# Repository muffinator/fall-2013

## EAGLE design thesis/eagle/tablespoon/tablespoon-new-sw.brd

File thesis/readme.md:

Welcome to the future of breadboarding

This is Butter

To operate the simulation files (rlc or ac.py), you need:
NGspice (nutmeg!) and you need to add it to your system path

Before looking at index.html, run an HTTP server from this directory.

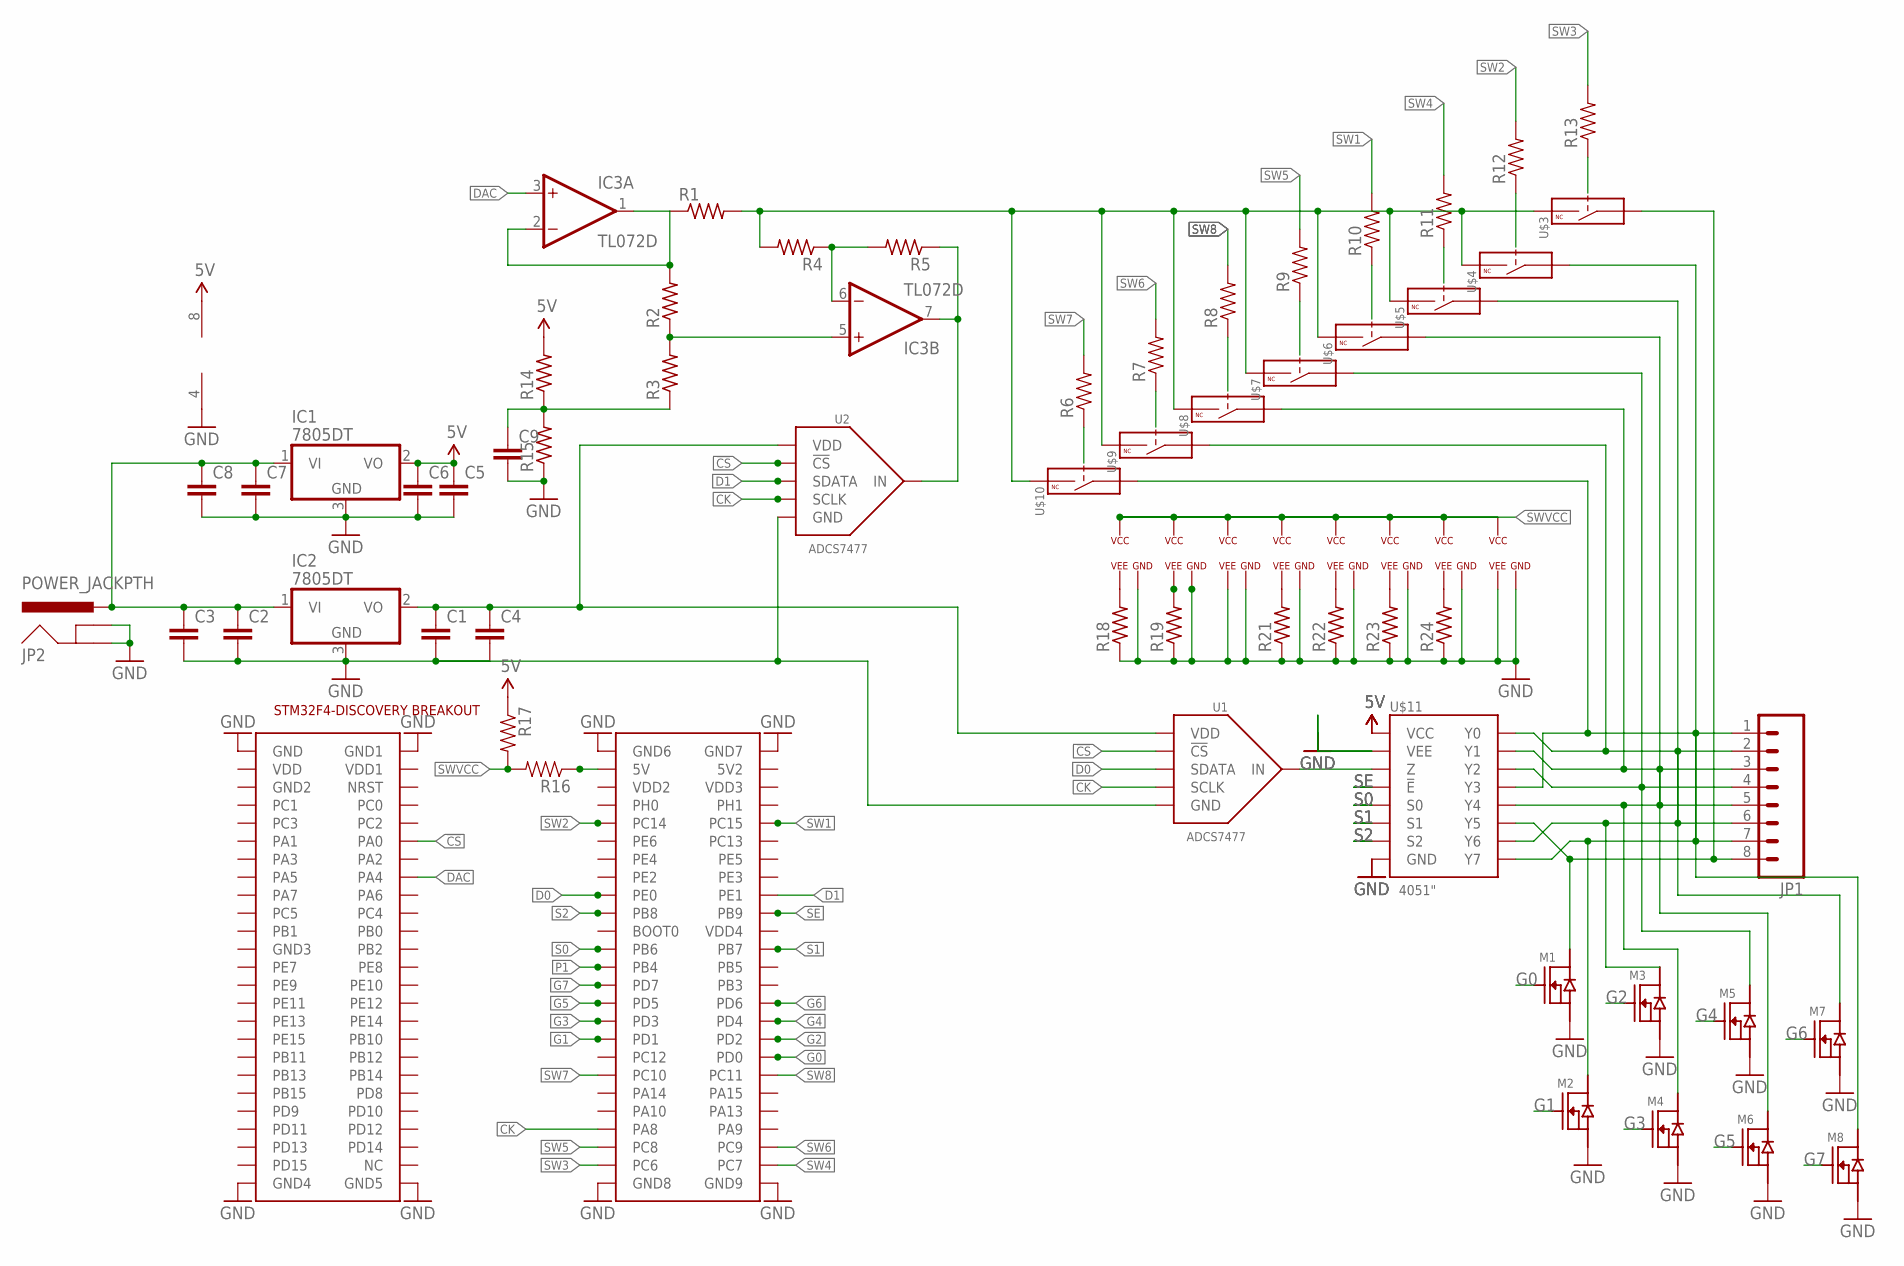
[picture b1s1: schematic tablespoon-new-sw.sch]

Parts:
C1, C2, C3, C4, C5, C6, C7, C8: C-EUC0805; C0805
C9: C-EUC0603; C0603
IC1, IC2: 7805DT; TO252
IC3: TL072D; SO08
JP1: M08LONGPADS; 1X08_LONGPADS
JP2: POWER_JACKPTH; POWER_JACK_PTH
M1, M2, M3, M4, M5, M6, M7, M8: N-FET; SOT23-3
R1, R2, R3, R4, R5, R14, R15, R18, R19, R21, R22, R23, R24: R-US_R0603; R0603
R6, R7, R8, R9, R10, R11, R12, R13, R16, R17: RESISTOR0805-RES; 0805
U1, U2: ADCS7477; SOT-23-6
U$1: STM32F4-DISCOVERY
U$3, U$4, U$5, U$6, U$7, U$8, U$9, U$10: DG467DG9422; TSSOP-6
U$11: 4051"; TSSOP-16

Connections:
4.6V: R16.1, U$1.P$53 (5V)
5V: C5.1, C6.1, IC1.2 (VO), IC3.8 (V+), R14.2, R17.1, U$11.P$16 (VCC)
!CS: U1.P$6 (!CS), U2.P$6 (!CS), U$1.P$12 (PA0)
CK: U1.P$4 (SCLK), U2.P$4 (SCLK), U$1.P$93 (PA8)
CUR: IC3.7 (OUT), R5.1, U2.P$3 (IN)
D0: U1.P$5 (SDATA), U$1.P$67 (PE0)
D1: U2.P$5 (SDATA), U$1.P$68 (PE1)
DAC: IC3.3 (+IN), U$1.P$16 (PA4)
G0: M1.1 (G), U$1.P$86 (PD0)
G1: M2.1 (G), U$1.P$83 (PD1)
G2: M3.1 (G), U$1.P$84 (PD2)
G3: M4.1 (G), U$1.P$81 (PD3)
G4: M5.1 (G), U$1.P$82 (PD4)
G5: M6.1 (G), U$1.P$79 (PD5)
G6: M7.1 (G), U$1.P$80 (PD6)
G7: M8.1 (G), U$1.P$77 (PD7)
GND: C1.2, C2.2, C3.2, C4.2, C5.2, C6.2, C7.2, C8.2, C9.2, IC1.3 (GND), IC2.3 (GND), IC3.4 (V-), JP2.GND, JP2.GNDBREAK, M1.2 (S), M2.2 (S), M3.2 (S), M4.2 (S), M5.2 (S), M6.2 (S), M7.2 (S), M8.2 (S), R15.1, R18.1, R19.1, R21.1, R22.1, R23.1, R24.1, U1.P$2 (GND), U2.P$2 (GND), U$1.P$1 (GND), U$1.P$2 (GND1), U$1.P$49 (GND4), U$1.P$50 (GND5), U$1.P$51 (GND6), U$1.P$52 (GND7), U$1.P$99 (GND8), U$1.P$100 (GND9), U$3.P$3 (VEE), U$3.P$4 (GND), U$4.P$4 (GND), U$5.P$4 (GND), U$6.P$4 (GND), U$7.P$4 (GND), U$8.P$4 (GND), U$9.P$4 (GND), U$10.P$3 (VEE), U$10.P$4 (GND), U$11.P$7 (VEE), U$11.P$8 (GND)
unnamed: JP1.2, M7.3 (D), U$9.P$2 (COM), U$11.P$13 (Y0)
unnamed: C1.1, C4.1, IC2.2 (VO), U1.P$1 (VDD), U2.P$1 (VDD)
unnamed: R6.1, U$10.P$6 (CTL)
unnamed: C2.1, C3.1, C7.1, C8.1, IC1.1 (VI), IC2.1 (VI), JP2.PWR
unnamed: JP1.3, M6.3 (D), U$8.P$2 (COM), U$11.P$14 (Y1)
unnamed: R7.1, U$9.P$6 (CTL)
unnamed: IC3.1 (OUT), IC3.2 (-IN), R1.1, R2.2
unnamed: JP1.1, M8.3 (D), U$10.P$2 (COM), U$11.P$12 (Y3)
unnamed: IC3.5 (+IN), R2.1, R3.2
unnamed: IC3.6 (-IN), R4.1, R5.2
unnamed: R8.1, U$8.P$6 (CTL)
unnamed: R1.2, R4.2, U$3.P$5 (IN), U$4.P$5 (IN), U$5.P$5 (IN), U$6.P$5 (IN), U$7.P$5 (IN), U$8.P$5 (IN), U$9.P$5 (IN), U$10.P$5 (IN)
unnamed: R9.1, U$7.P$6 (CTL)
unnamed: R12.1, U$4.P$6 (CTL)
unnamed: R13.1, U$3.P$6 (CTL)
unnamed: R11.1, U$5.P$6 (CTL)
unnamed: R10.1, U$6.P$6 (CTL)
unnamed: JP1.8, M1.3 (D), U$3.P$2 (COM), U$11.P$5 (Y5)
unnamed: C9.1, R3.1, R14.1, R15.2
unnamed: U1.P$3 (IN), U$11.P$3 (Z)
unnamed: JP1.7, M2.3 (D), U$4.P$2 (COM), U$11.P$4 (Y7)
unnamed: JP1.6, M3.3 (D), U$5.P$2 (COM), U$11.P$2 (Y6)
unnamed: JP1.5, M4.3 (D), U$6.P$2 (COM), U$11.P$1 (Y4)
unnamed: JP1.4, M5.3 (D), U$7.P$2 (COM), U$11.P$15 (Y2)
unnamed: R18.2, U$9.P$3 (VEE)
unnamed: R19.2, U$8.P$3 (VEE)
unnamed: R21.2, U$4.P$3 (VEE)
unnamed: R22.2, U$5.P$3 (VEE)
unnamed: R23.2, U$6.P$3 (VEE)
unnamed: R24.2, U$7.P$3 (VEE)
P1: U$1.P$75 (PB4)
S0: U$1.P$73 (PB6), U$11.P$11 (S0)
S1: U$1.P$74 (PB7), U$11.P$10 (S1)
S2: U$1.P$69 (PB8), U$11.P$9 (S2)
SE: U$1.P$70 (PB9), U$11.P$6 (!E)
SW1: R10.2, U$1.P$60 (PC15)
SW2: R12.2, U$1.P$59 (PC14)
SW3: R13.2, U$1.P$97 (PC6)
SW4: R11.2, U$1.P$98 (PC7)
SW5: R9.2, U$1.P$95 (PC8)
SW6: R7.2, U$1.P$96 (PC9)
SW7: R6.2, U$1.P$87 (PC10)
SW8: R8.2, U$1.P$88 (PC11)
SWVCC: R16.2, R17.2, U$3.P$1 (VCC), U$4.P$1 (VCC), U$5.P$1 (VCC), U$6.P$1 (VCC), U$7.P$1 (VCC), U$8.P$1 (VCC), U$9.P$1 (VCC), U$10.P$1 (VCC)

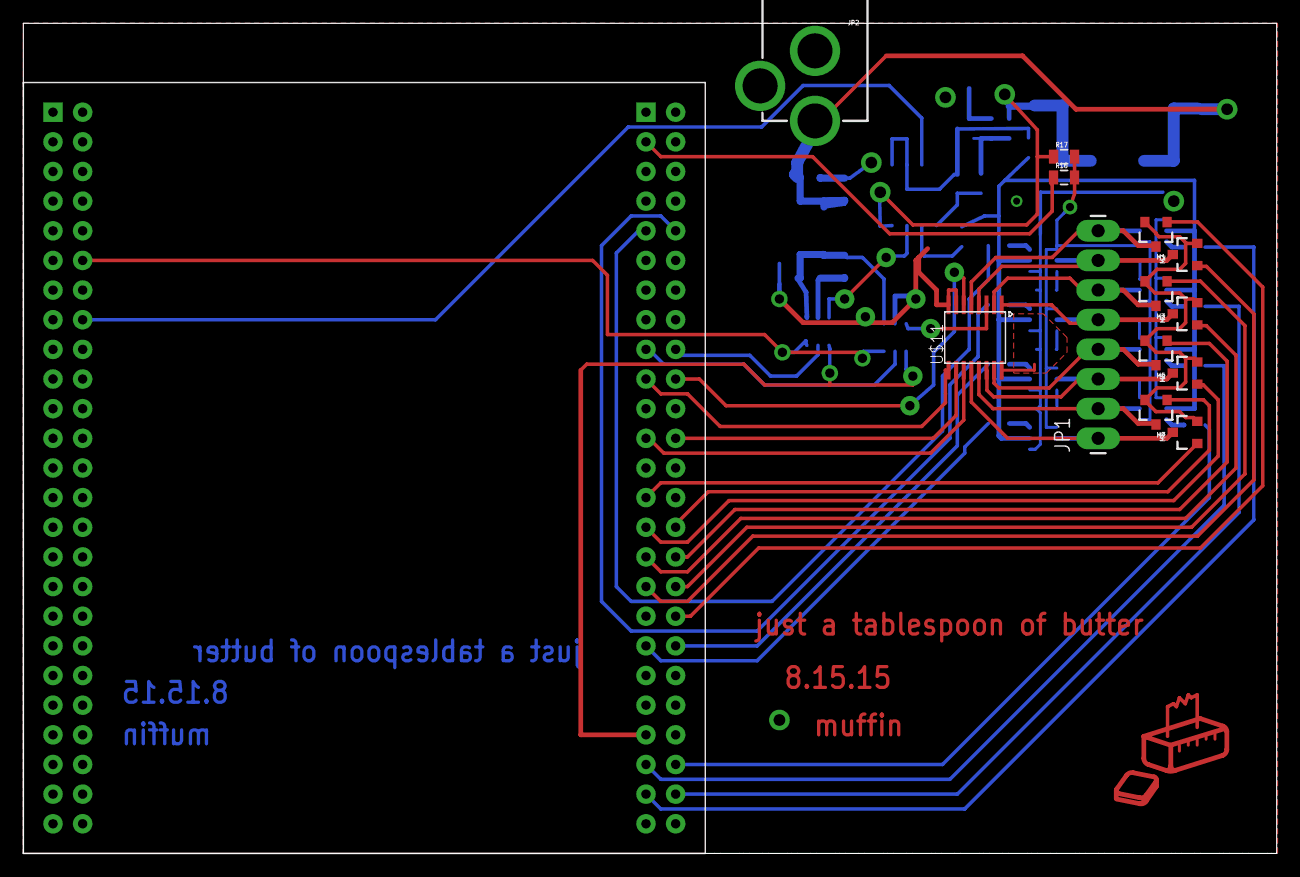
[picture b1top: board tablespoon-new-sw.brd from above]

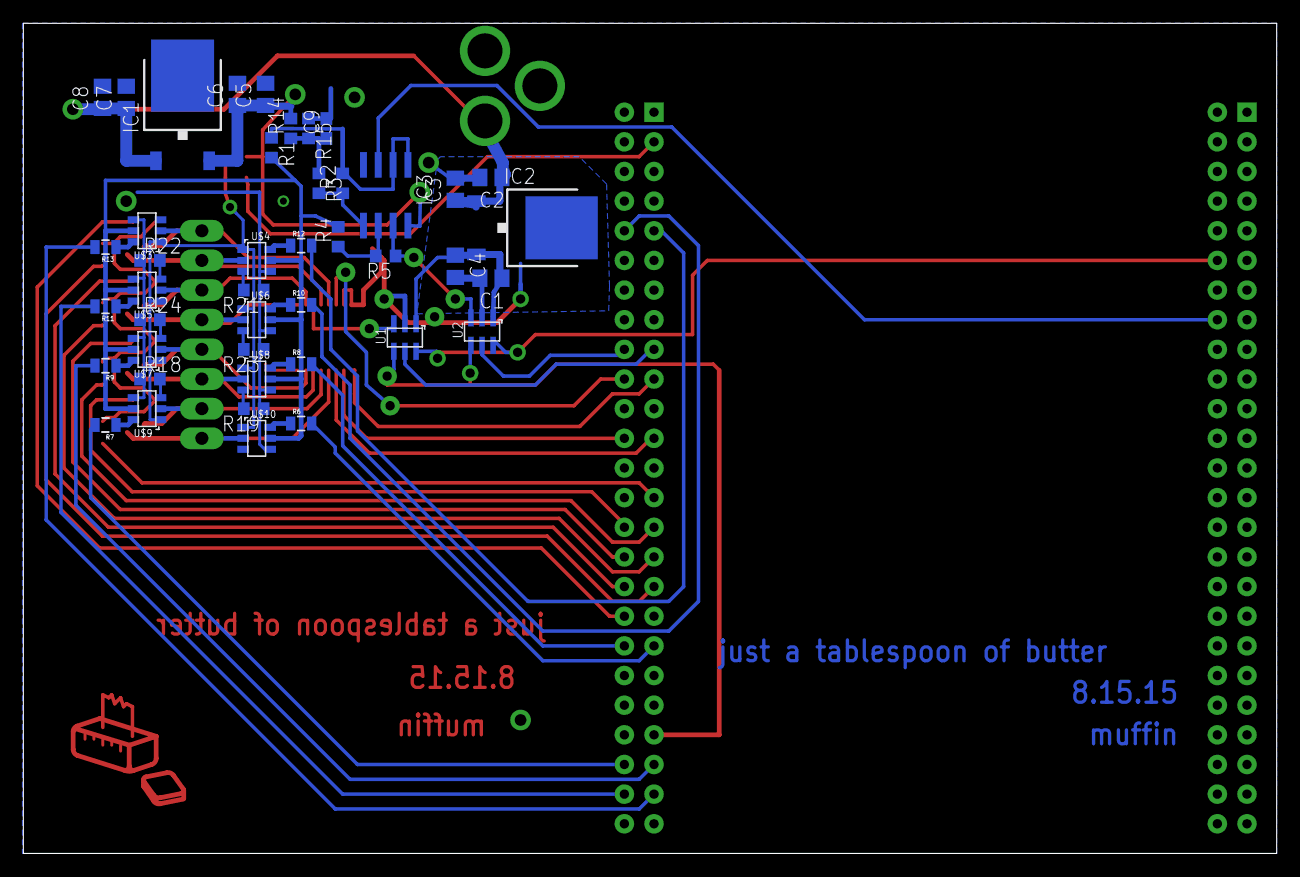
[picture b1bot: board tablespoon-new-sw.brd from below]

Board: 2 copper layers, 107.4 x 71.1 mm, 57 parts (43 on the bottom side), 60 nets.

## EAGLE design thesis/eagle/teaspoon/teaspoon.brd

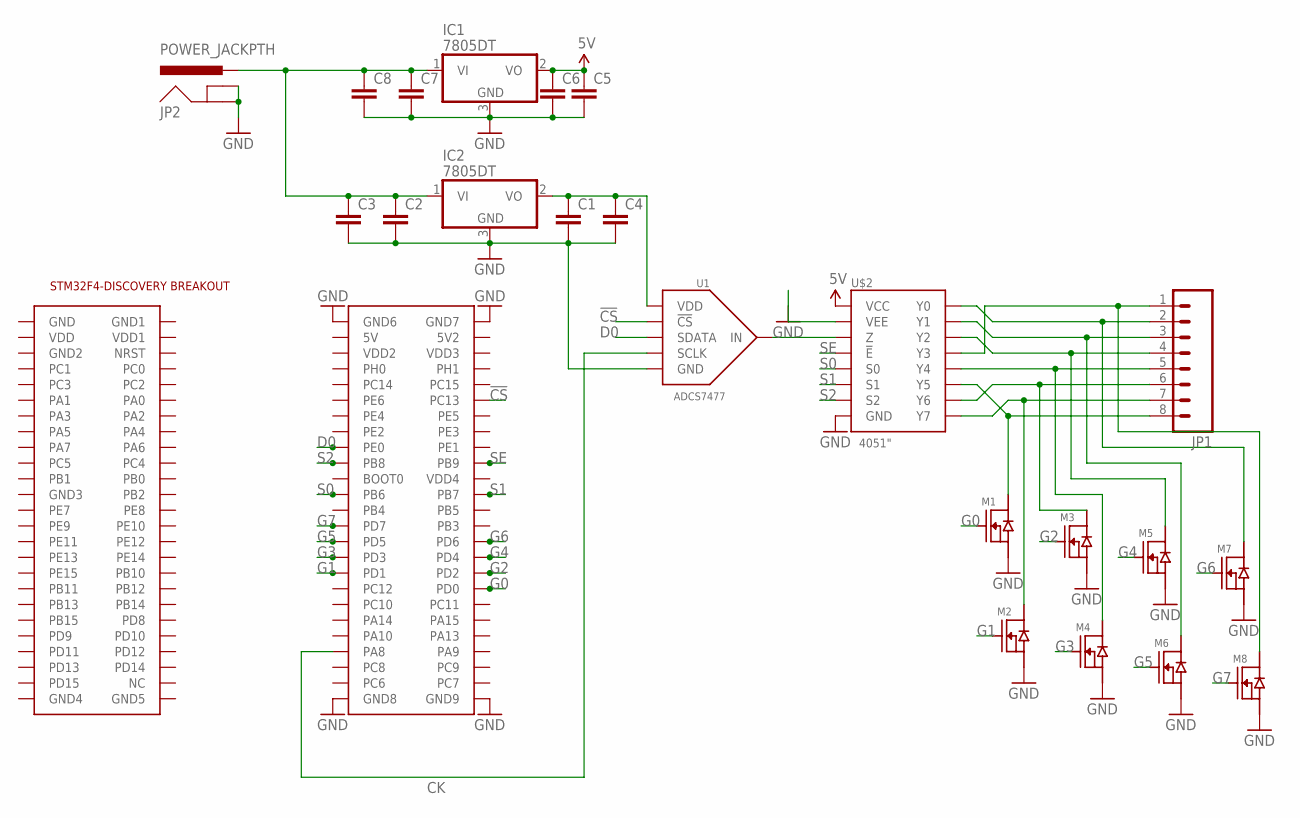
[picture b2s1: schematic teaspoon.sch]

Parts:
C1, C2, C3, C4, C5, C6, C7, C8: C-EUC0805; C0805
IC1, IC2: 7805DT; TO252
JP1: M08LONGPADS; 1X08_LONGPADS
JP2: POWER_JACKPTH; POWER_JACK_PTH
M1, M2, M3, M4, M5, M6, M7, M8: N-FET; SOT23-3
U1: ADCS7477; SOT-23-6
U$1: STM32F4-DISCOVERY
U$2: 4051"; TSSOP-16

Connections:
5V: C5.1, C6.1, IC1.2 (VO), U$2.P$16 (VCC)
!CS: U1.P$6 (!CS), U$1.P$62 (PC13)
CK: U1.P$4 (SCLK), U$1.P$93 (PA8)
D0: U1.P$5 (SDATA), U$1.P$67 (PE0)
G0: M1.1 (G), U$1.P$86 (PD0)
G1: M2.1 (G), U$1.P$83 (PD1)
G2: M3.1 (G), U$1.P$84 (PD2)
G3: M4.1 (G), U$1.P$81 (PD3)
G4: M5.1 (G), U$1.P$82 (PD4)
G5: M6.1 (G), U$1.P$79 (PD5)
G6: M7.1 (G), U$1.P$80 (PD6)
G7: M8.1 (G), U$1.P$77 (PD7)
GND: C1.2, C2.2, C3.2, C4.2, C5.2, C6.2, C7.2, C8.2, IC1.3 (GND), IC2.3 (GND), JP2.GND, JP2.GNDBREAK, M1.2 (S), M2.2 (S), M3.2 (S), M4.2 (S), M5.2 (S), M6.2 (S), M7.2 (S), M8.2 (S), U1.P$2 (GND), U$1.P$51 (GND6), U$1.P$52 (GND7), U$1.P$99 (GND8), U$1.P$100 (GND9), U$2.P$7 (VEE), U$2.P$8 (GND)
unnamed: U1.P$3 (IN), U$2.P$3 (Z)
unnamed: C1.1, C4.1, IC2.2 (VO), U1.P$1 (VDD)
unnamed: C2.1, C3.1, C7.1, C8.1, IC1.1 (VI), IC2.1 (VI), JP2.PWR
unnamed: JP1.1, M8.3 (D), U$2.P$12 (Y3)
unnamed: JP1.2, M7.3 (D), U$2.P$13 (Y0)
unnamed: JP1.3, M6.3 (D), U$2.P$14 (Y1)
unnamed: JP1.4, M5.3 (D), U$2.P$15 (Y2)
unnamed: JP1.5, M4.3 (D), U$2.P$1 (Y4)
unnamed: JP1.6, M3.3 (D), U$2.P$2 (Y6)
unnamed: JP1.7, M2.3 (D), U$2.P$4 (Y7)
unnamed: JP1.8, M1.3 (D), U$2.P$5 (Y5)
S0: U$1.P$73 (PB6), U$2.P$11 (S0)
S1: U$1.P$74 (PB7), U$2.P$10 (S1)
S2: U$1.P$69 (PB8), U$2.P$9 (S2)
SE: U$1.P$70 (PB9), U$2.P$6 (!E)

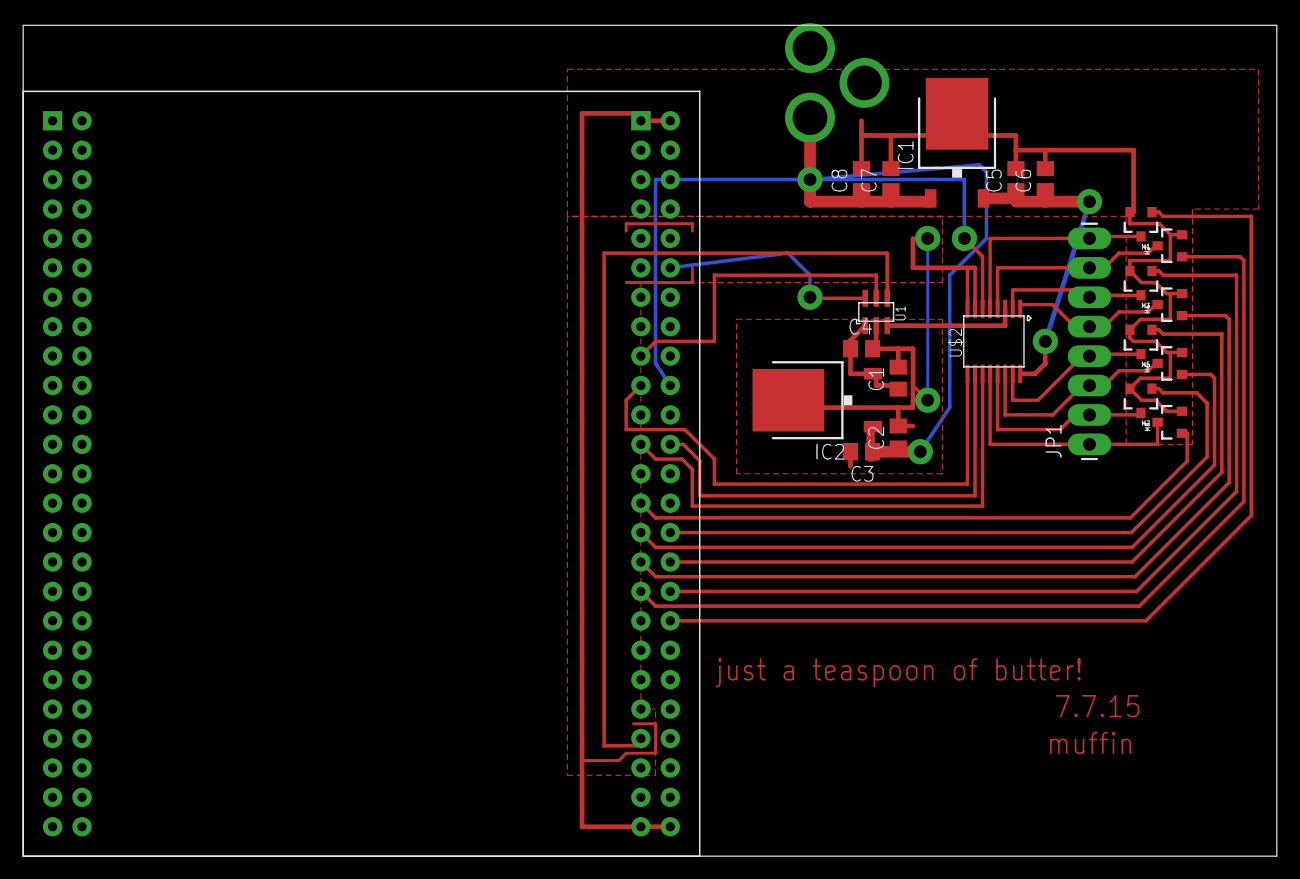
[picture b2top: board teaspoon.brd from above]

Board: 2 copper layers, 108.3 x 71.7 mm, 23 parts (1 on the bottom side), 28 nets.

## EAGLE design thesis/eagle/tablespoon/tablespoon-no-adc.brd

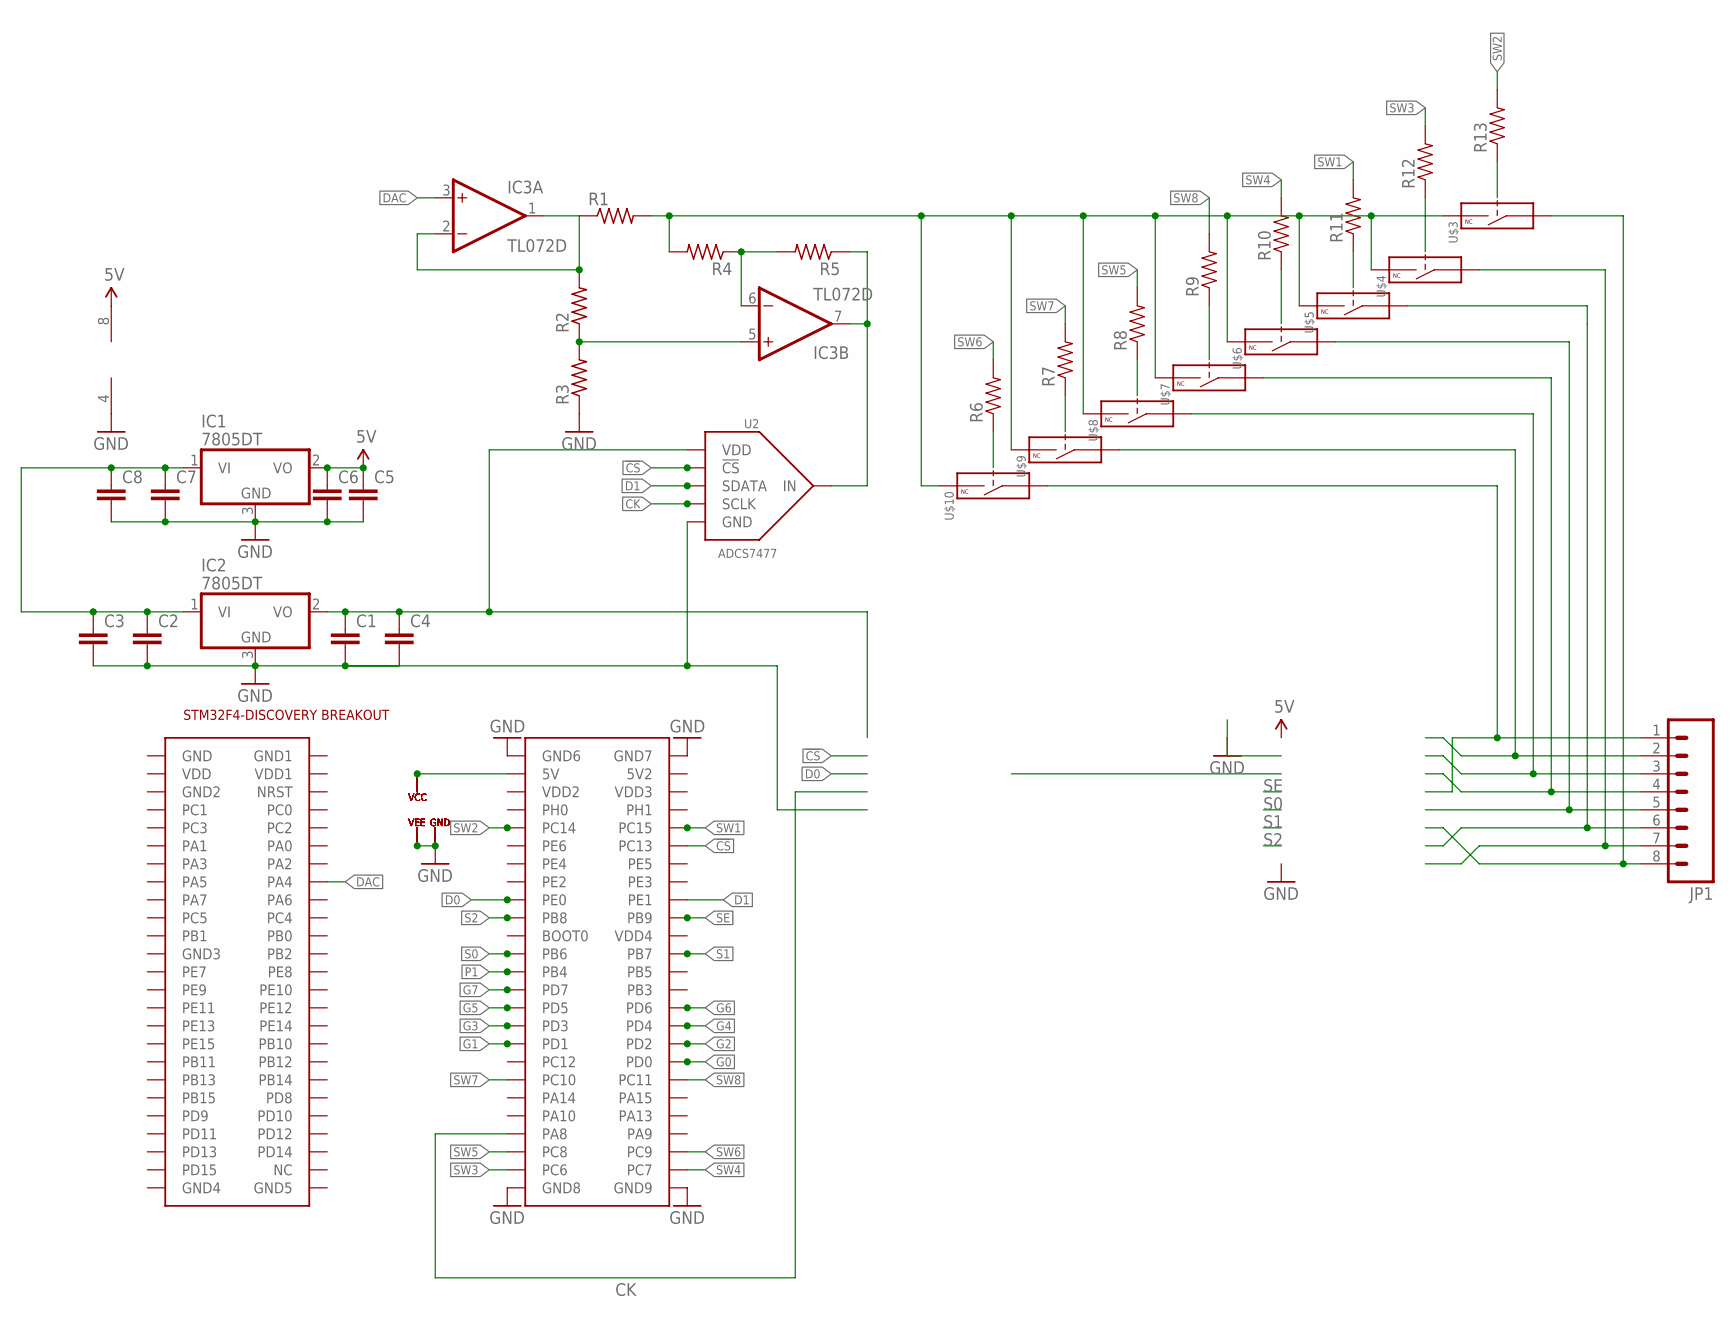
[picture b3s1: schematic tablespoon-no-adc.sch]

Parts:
C1, C2, C3, C4, C5, C6, C7, C8: C-EUC0805; C0805
IC1, IC2: 7805DT; TO252
IC3: TL072D; SO08
JP1: M08LONGPADS; 1X08_LONGPADS
R1, R2, R3, R4, R5: R-US_R0603; R0603
R6, R7, R8, R9, R10, R11, R12, R13: RESISTOR0805-RES; 0805
U2: ADCS7477; SOT-23-6
U$1: STM32F4-DISCOVERY
U$3, U$4, U$5, U$6, U$7, U$8, U$9, U$10: DG467; TSSOP-6

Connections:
4.6V: U$1.P$53 (5V), U$3.P$5 (VCC), U$4.P$5 (VCC), U$5.P$5 (VCC), U$6.P$5 (VCC), U$7.P$5 (VCC), U$8.P$5 (VCC), U$9.P$5 (VCC), U$10.P$5 (VCC)
5V: C5.1, C6.1, IC1.2 (VO), IC3.8 (V+)
!CS: U2.P$6 (!CS), U$1.P$62 (PC13)
CK: U2.P$4 (SCLK), U$1.P$93 (PA8)
CUR: IC3.7 (OUT), R5.1, U2.P$3 (IN)
D0: U$1.P$67 (PE0)
D1: U2.P$5 (SDATA), U$1.P$68 (PE1)
DAC: IC3.3 (+IN), U$1.P$16 (PA4)
G0: U$1.P$86 (PD0)
G1: U$1.P$83 (PD1)
G2: U$1.P$84 (PD2)
G3: U$1.P$81 (PD3)
G4: U$1.P$82 (PD4)
G5: U$1.P$79 (PD5)
G6: U$1.P$80 (PD6)
G7: U$1.P$77 (PD7)
GND: C1.2, C2.2, C3.2, C4.2, C5.2, C6.2, C7.2, C8.2, IC1.3 (GND), IC2.3 (GND), IC3.4 (V-), R3.1, U2.P$2 (GND), U$1.P$51 (GND6), U$1.P$52 (GND7), U$1.P$99 (GND8), U$1.P$100 (GND9), U$3.P$2 (VEE), U$3.P$4 (GND), U$4.P$2 (VEE), U$4.P$4 (GND), U$5.P$2 (VEE), U$5.P$4 (GND), U$6.P$2 (VEE), U$6.P$4 (GND), U$7.P$2 (VEE), U$7.P$4 (GND), U$8.P$2 (VEE), U$8.P$4 (GND), U$9.P$2 (VEE), U$9.P$4 (GND), U$10.P$2 (VEE), U$10.P$4 (GND)
unnamed: C1.1, C4.1, IC2.2 (VO), U2.P$1 (VDD)
unnamed: R6.1, U$10.P$3 (CTL)
unnamed: C2.1, C3.1, C7.1, C8.1, IC1.1 (VI), IC2.1 (VI)
unnamed: JP1.4, U$7.P$6 (COM)
unnamed: R7.1, U$9.P$3 (CTL)
unnamed: IC3.1 (OUT), IC3.2 (-IN), R1.1, R2.2
unnamed: JP1.5, U$6.P$6 (COM)
unnamed: JP1.3, U$8.P$6 (COM)
unnamed: JP1.1, U$10.P$6 (COM)
unnamed: JP1.2, U$9.P$6 (COM)
unnamed: IC3.5 (+IN), R2.1, R3.2
unnamed: IC3.6 (-IN), R4.1, R5.2
unnamed: R8.1, U$8.P$3 (CTL)
unnamed: R1.2, R4.2, U$3.P$1 (IN), U$4.P$1 (IN), U$5.P$1 (IN), U$6.P$1 (IN), U$7.P$1 (IN), U$8.P$1 (IN), U$9.P$1 (IN), U$10.P$1 (IN)
unnamed: R9.1, U$7.P$3 (CTL)
unnamed: R12.1, U$4.P$3 (CTL)
unnamed: R13.1, U$3.P$3 (CTL)
unnamed: R11.1, U$5.P$3 (CTL)
unnamed: R10.1, U$6.P$3 (CTL)
unnamed: JP1.6, U$5.P$6 (COM)
unnamed: JP1.7, U$4.P$6 (COM)
unnamed: JP1.8, U$3.P$6 (COM)
P1: U$1.P$75 (PB4)
S0: U$1.P$73 (PB6)
S1: U$1.P$74 (PB7)
S2: U$1.P$69 (PB8)
SE: U$1.P$70 (PB9)
SW1: R11.2, U$1.P$60 (PC15)
SW2: R13.2, U$1.P$59 (PC14)
SW3: R12.2, U$1.P$97 (PC6)
SW4: R10.2, U$1.P$98 (PC7)
SW5: R8.2, U$1.P$95 (PC8)
SW6: R6.2, U$1.P$96 (PC9)
SW7: R7.2, U$1.P$87 (PC10)
SW8: R9.2, U$1.P$88 (PC11)

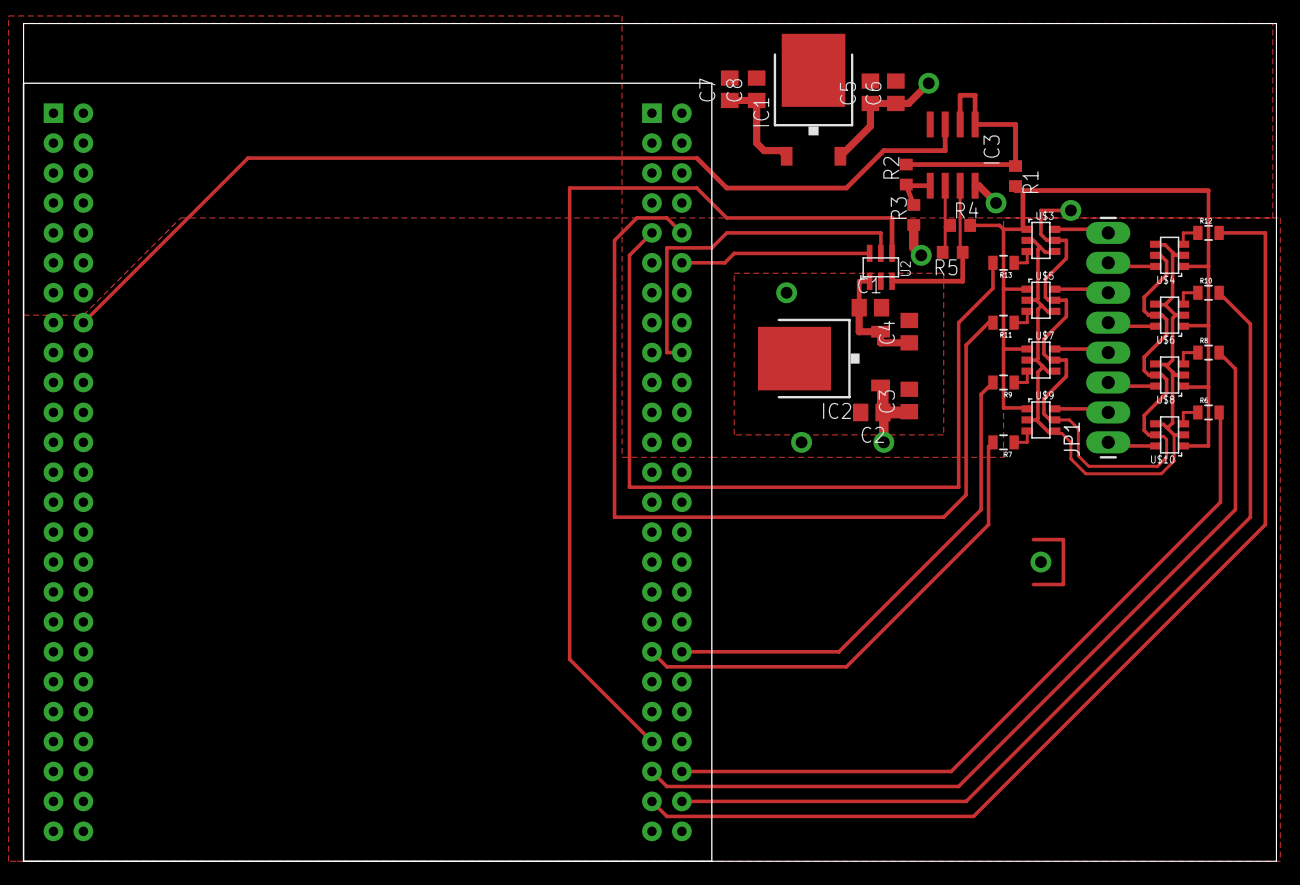
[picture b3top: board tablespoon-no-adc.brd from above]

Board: 2 copper layers, 106.3 x 71.1 mm, 35 parts (0 on the bottom side), 38 nets.

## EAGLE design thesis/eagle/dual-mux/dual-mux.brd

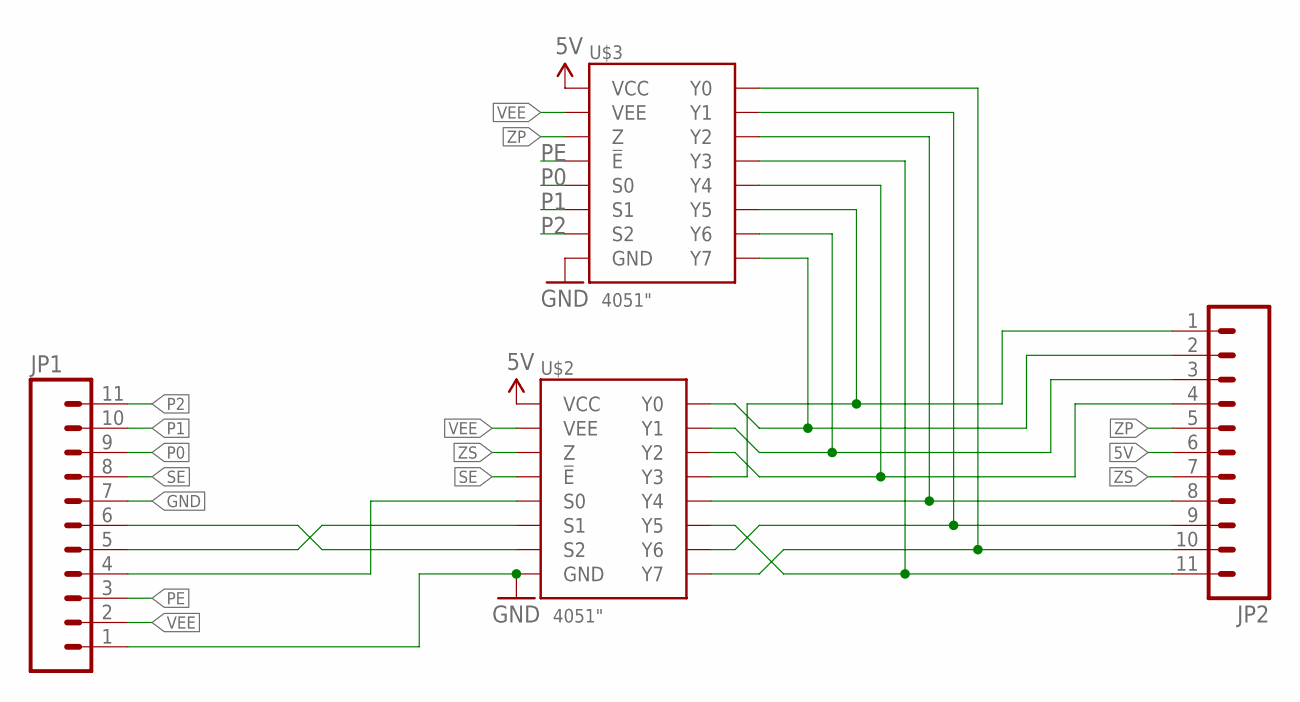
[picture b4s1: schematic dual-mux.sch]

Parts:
JP1, JP2: M11LONGPADS; 1X11_LONGPADS
U$2, U$3: 4051"; TSSOP-16

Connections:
5V: JP2.6, U$2.P$16 (VCC), U$3.P$16 (VCC)
GND: JP1.1, JP1.7, U$2.P$8 (GND), U$3.P$8 (GND)
unnamed: JP2.4, U$2.P$15 (Y2), U$3.P$1 (Y4)
unnamed: JP2.10, U$2.P$4 (Y7), U$3.P$13 (Y0)
unnamed: JP2.8, U$2.P$1 (Y4), U$3.P$15 (Y2)
unnamed: JP2.11, U$2.P$5 (Y5), U$3.P$12 (Y3)
unnamed: JP2.1, U$2.P$12 (Y3), U$3.P$5 (Y5)
unnamed: JP2.2, U$2.P$13 (Y0), U$3.P$4 (Y7)
unnamed: JP2.3, U$2.P$14 (Y1), U$3.P$2 (Y6)
unnamed: JP2.9, U$2.P$2 (Y6), U$3.P$14 (Y1)
P0: JP1.9, U$3.P$11 (S0)
P1: JP1.10, U$3.P$10 (S1)
P2: JP1.11, U$3.P$9 (S2)
PE: JP1.3, U$3.P$6 (!E)
S0: JP1.4, U$2.P$11 (S0)
S1: JP1.5, U$2.P$10 (S1)
S2: JP1.6, U$2.P$9 (S2)
SE: JP1.8, U$2.P$6 (!E)
VEE: JP1.2, U$2.P$7 (VEE), U$3.P$7 (VEE)
ZP: JP2.5, U$3.P$3 (Z)
ZS: JP2.7, U$2.P$3 (Z)

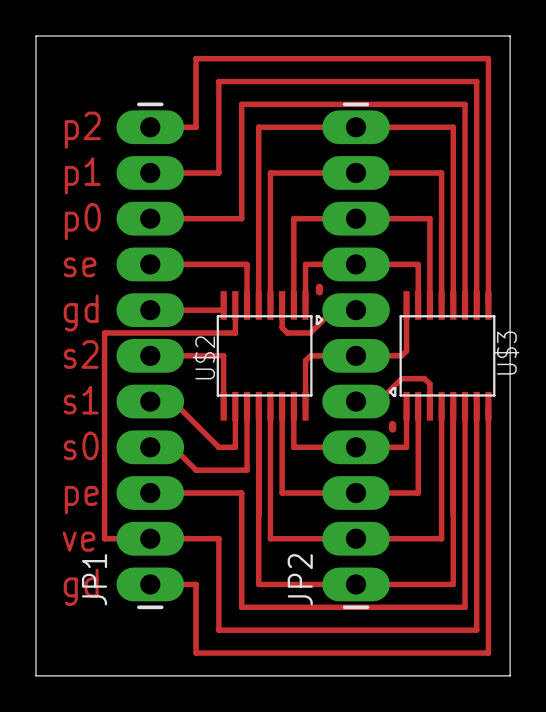
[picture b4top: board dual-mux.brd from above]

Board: 2 copper layers, 26.3 x 35.5 mm, 4 parts (0 on the bottom side), 21 nets.

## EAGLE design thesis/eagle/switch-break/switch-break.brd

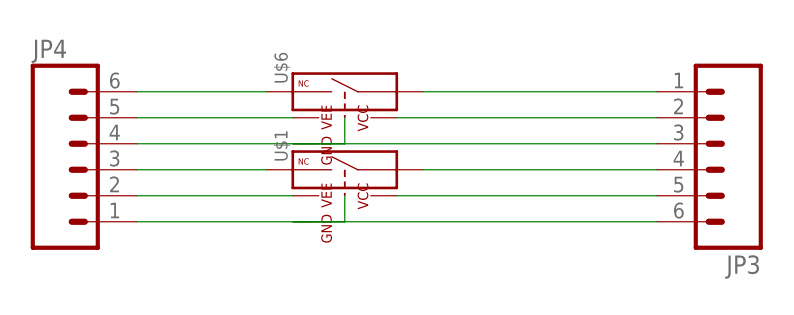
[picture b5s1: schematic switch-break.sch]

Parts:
JP3, JP4: M06LONGPADS; 1X06_LONGPADS
U$1, U$6: DG467; TSSOP-6

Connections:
unnamed: JP3.3, U$6.P$4 (GND)
unnamed: JP4.4, U$6.P$3 (CTL)
unnamed: JP3.2, U$6.P$5 (VCC)
unnamed: JP3.4, U$1.P$6 (COM)
unnamed: JP3.1, U$6.P$6 (COM)
unnamed: JP4.5, U$6.P$2 (VEE)
unnamed: JP4.3, U$1.P$1 (IN)
unnamed: JP3.5, U$1.P$5 (VCC)
unnamed: JP4.2, U$1.P$2 (VEE)
unnamed: JP3.6, U$1.P$4 (GND)
unnamed: JP4.1, U$1.P$3 (CTL)
unnamed: JP4.6, U$6.P$1 (IN)

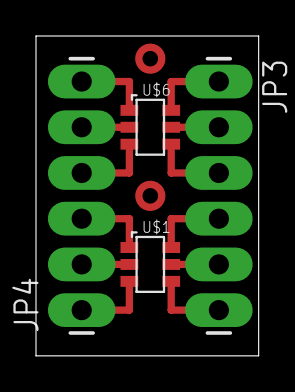
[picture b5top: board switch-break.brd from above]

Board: 2 copper layers, 12.4 x 17.8 mm, 4 parts (0 on the bottom side), 12 nets.

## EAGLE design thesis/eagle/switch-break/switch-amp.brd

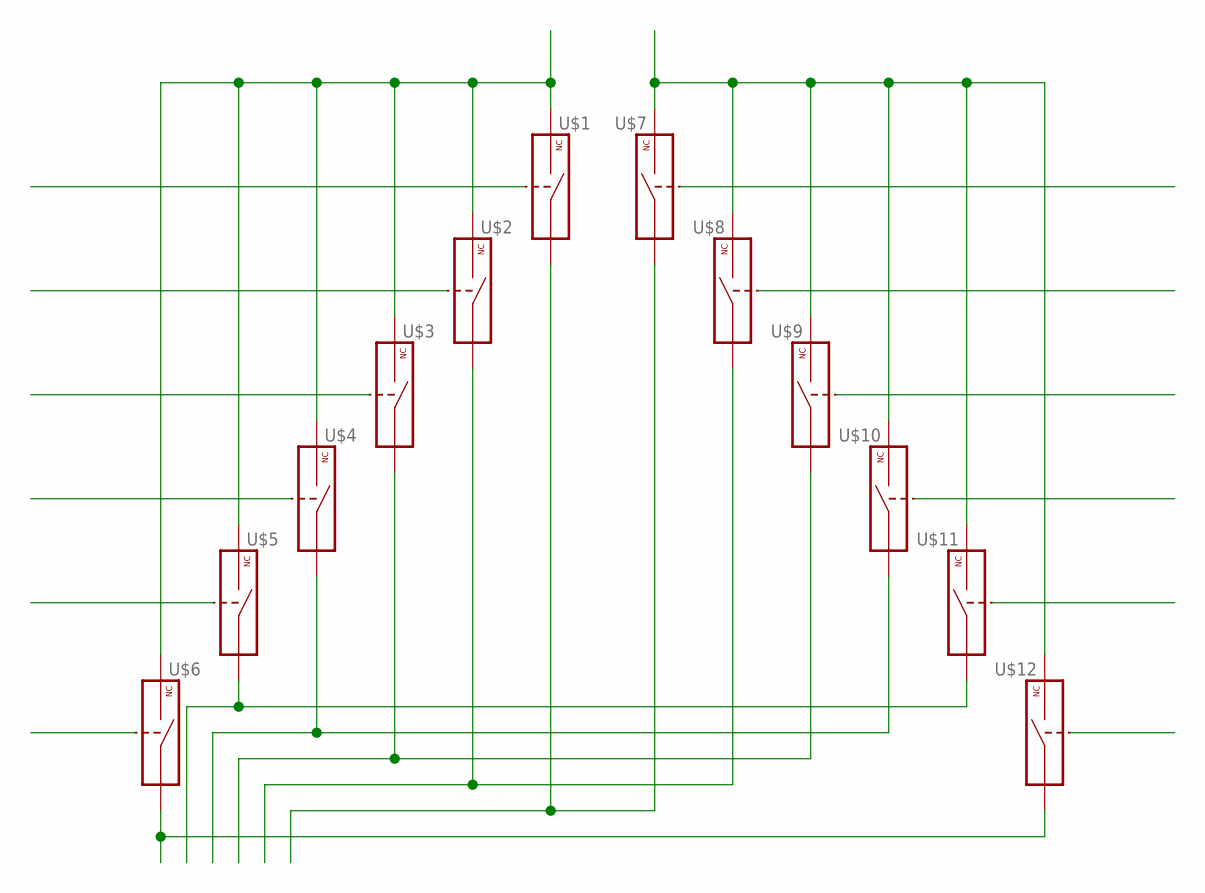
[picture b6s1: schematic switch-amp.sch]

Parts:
U$1, U$2, U$3, U$4, U$5, U$6, U$7, U$8, U$9, U$10, U$11, U$12: DG467; TSSOP-6

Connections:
unnamed: U$1.P$1 (IN), U$2.P$1 (IN), U$3.P$1 (IN), U$4.P$1 (IN), U$5.P$1 (IN), U$6.P$1 (IN)
unnamed: U$5.P$6 (COM), U$11.P$6 (COM)
unnamed: U$4.P$6 (COM), U$10.P$6 (COM)
unnamed: U$3.P$6 (COM), U$9.P$6 (COM)
unnamed: U$2.P$6 (COM), U$8.P$6 (COM)
unnamed: U$7.P$1 (IN), U$8.P$1 (IN), U$9.P$1 (IN), U$10.P$1 (IN), U$11.P$1 (IN), U$12.P$1 (IN)
unnamed: U$6.P$6 (COM), U$12.P$6 (COM)
unnamed: U$1.P$6 (COM), U$7.P$6 (COM)

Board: 2 copper layers, 12 parts (0 on the bottom side), 8 nets, no tracks yet.

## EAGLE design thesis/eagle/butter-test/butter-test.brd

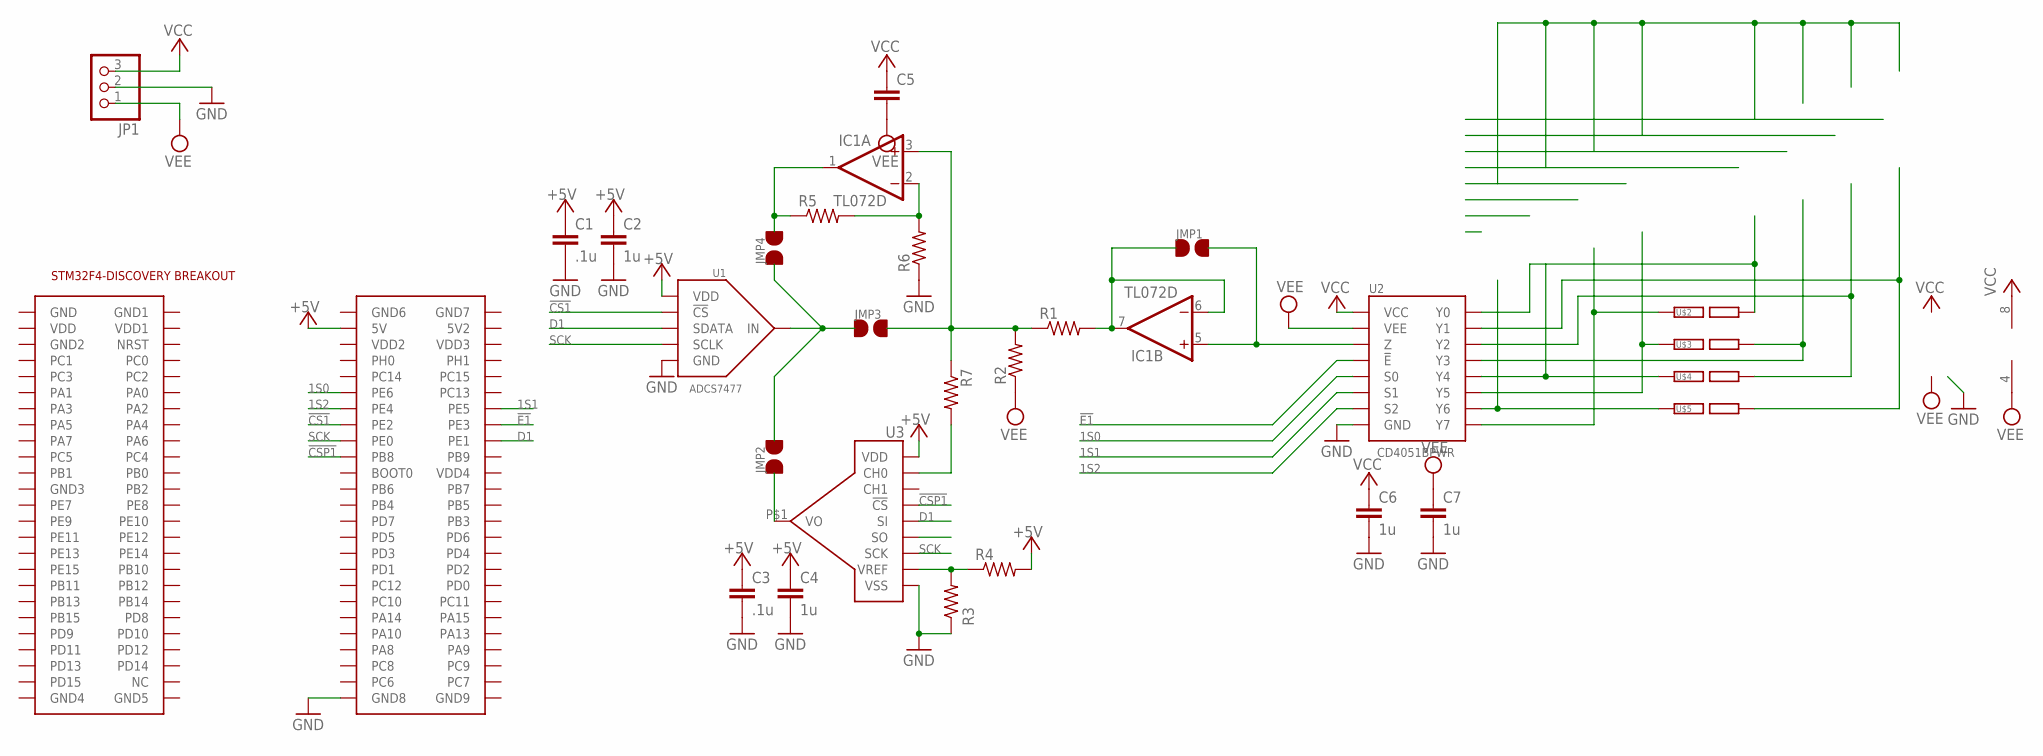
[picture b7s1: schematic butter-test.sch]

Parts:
C1, C3: .1u; C0805
C2, C4, C6, C7: 1u; C0805
C5: C-EUC0805; C0805
IC1: TL072D; SO08
JMP1, JMP2, JMP3, JMP4: JMP
JP1: PINHD-1X3; 1X03
R1, R2, R3, R4, R5, R6, R7: R-US_R0603; R0603
U1: ADCS7477; SOT-23-6
U2: CD4051BPWR; TSSOP-16
U3: MCP6S93; MSOP-10
U$1: STM32F4-DISCOVERY
U$2, U$3, U$4, U$5: RAILSEP; RAIL

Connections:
1S0: U2.P$11 (S0), U$1.P$61 (PE6)
1S1: U2.P$10 (S1), U$1.P$64 (PE5)
1S2: U2.P$9 (S2), U$1.P$63 (PE4)
!CS1: U1.P$6 (!CS), U$1.P$65 (PE2)
!CSP1: U3.P$6 (!CS), U$1.P$69 (PB8)
!E1: U2.P$6 (!E), U$1.P$66 (PE3)
+5V: C1.1, C2.1, C3.1, C4.1, R4.2, U1.P$1 (VDD), U3.P$10 (VDD), U$1.P$53 (5V)
D1: U1.P$5 (SDATA), U3.P$7 (SI), U$1.P$68 (PE1)
GND: C1.2, C2.2, C3.2, C4.2, C6.2, C7.2, JP1.2, R3.1, R6.1, U1.P$2 (GND), U2.P$8 (GND), U3.P$5 (VSS), U$1.P$99 (GND8)
unnamed: IC1.2 (-IN), R5.2, R6.2
unnamed: U2.P$13 (Y0), U$2.P$R (R)
unnamed: U2.P$5 (Y5), U$3.P$L (L)
unnamed: IC1.5 (+IN), JMP1.P$2, U2.P$3 (Z)
unnamed: JMP2.P$1, U3.P$1 (VO)
unnamed: IC1.6 (-IN), IC1.7 (OUT), JMP1.P$1, R1.2
unnamed: U2.P$4 (Y7), U$2.P$L (L)
unnamed: U2.P$12 (Y3), U$3.P$R (R)
unnamed: U2.P$1 (Y4), U$4.P$L (L)
unnamed: U2.P$15 (Y2), U$4.P$R (R)
unnamed: U2.P$2 (Y6), U$5.P$L (L)
unnamed: U2.P$14 (Y1), U$5.P$R (R)
unnamed: IC1.3 (+IN), JMP3.P$2, R1.1, R2.2, R7.1
unnamed: R3.2, R4.1, U3.P$4 (VREF)
unnamed: JMP2.P$2, JMP3.P$1, JMP4.P$1, U1.P$3 (IN)
unnamed: IC1.1 (OUT), JMP4.P$2, R5.1
unnamed: R7.2, U3.P$2 (CH0)
SCK: U1.P$4 (SCLK), U3.P$9 (SCK), U$1.P$67 (PE0)
VCC: C5.1, C6.1, IC1.8 (V+), JP1.3, U2.P$16 (VCC)
VEE: C5.2, C7.1, IC1.4 (V-), JP1.1, R2.1, U2.P$7 (VEE)

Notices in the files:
parts and their libraries:
SparkFun-Connectors: Licensing: Creative Commons ShareAlike 4.0 International - https://creativecommons.org/licenses/by-sa/4.0
